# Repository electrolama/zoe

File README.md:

# zoe

A PoE powered Zigbee dev kit with RTC for Raspberry Pi.

Details at [electrolama.com/p/zoe](https://electrolama.com/projects/zoe).

zoe is designed by Electrolama / Omer Kilic and licensed under the [Solderpad Hardware License 2.0](https://solderpad.org/licenses/SHL-2.0/).

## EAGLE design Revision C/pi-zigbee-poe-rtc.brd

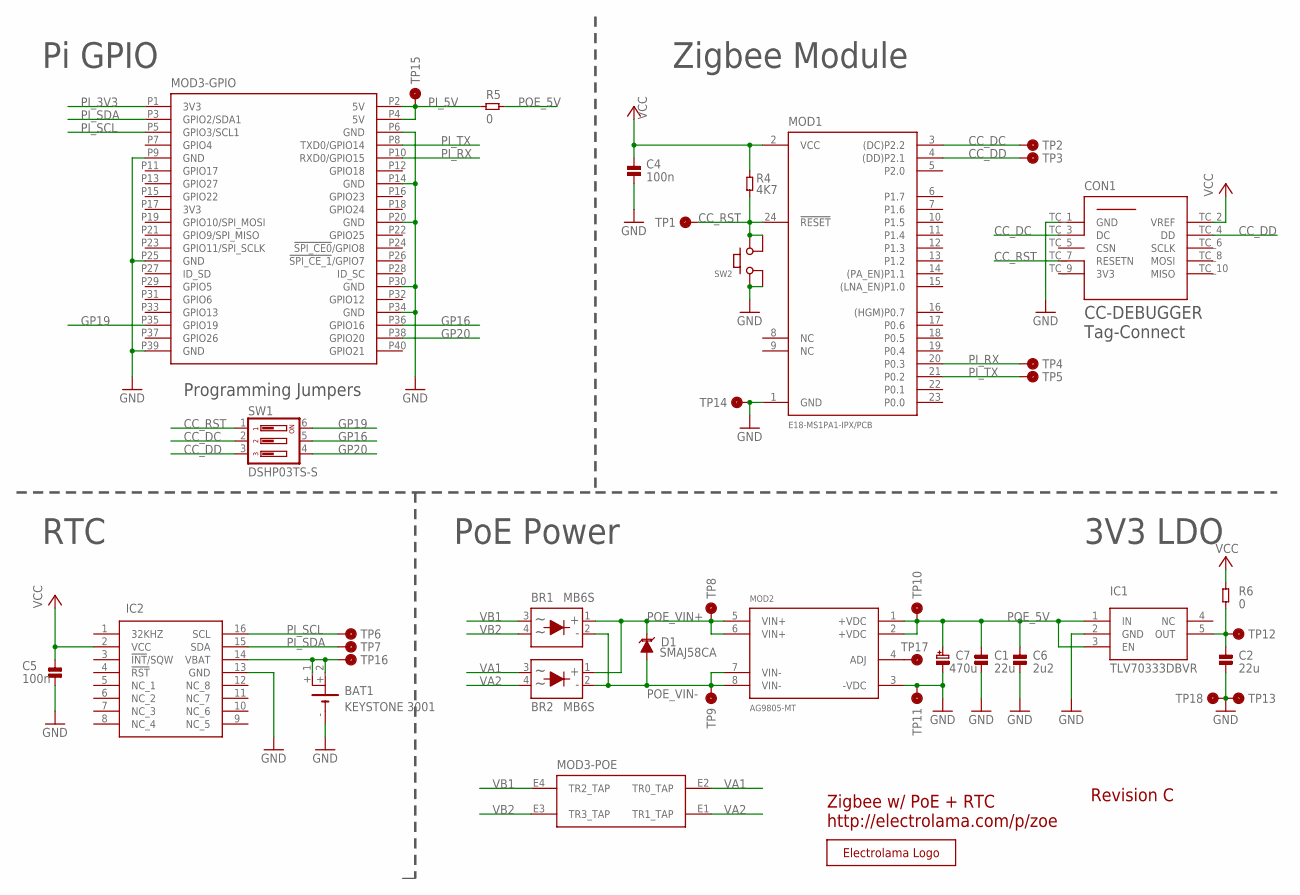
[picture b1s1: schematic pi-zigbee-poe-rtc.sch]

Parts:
BAT1: KEYSTONE 3001; KEYSTONE_3001
BR1, BR2: MB6S; SOP254P665X270-4N
C1, C2: 22u; _PKG_C_0805
C4, C5: 100n; _PKG_C_0603
C6: 2u2; _PKG_C_0603
C7: 470u; _CAP_ELCO_D8_L10.5
CON1: TC2050-IDC-NL_CC-DEBUGGER; TC2050-IDC-NL
D1: SMAJ58CA; DIOM5126X250N-NOPOL
IC1: TLV70333DBVR; SOT95P280X145-5N
IC2: RTC-DS3231SN#; SOIC127P1032X265-16N
MOD1: E18-MS1PA1-IPX/PCB; EBYTE-E18-MS1PA1
MOD2: AG9805-MT; SILVERTEL_AG9800M
MOD3: RPI-HAT-FULL
R4: 4K7; _PKG_C_0603
R5, R6: 0; TP_DUAL_1206
SW1: DSHP03TS-S
SW2: SPNO-XKB-TS-1187A; XKB-TS-1187A
TP1, TP2, TP3, TP4, TP5, TP6, TP7, TP8, TP9, TP10, TP11, TP12, TP13, TP14, TP15, TP16, TP17: TP; TP_DOT
TP18: TP-HOOK; TP_S2751-46R
U$1: LOGO-ELECTROLAMA; ELECTROLAMA

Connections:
CC_DC: CON1.TC_3 (DC), MOD1.3 ((DC)P2.2), SW1.2, TP2.TP
CC_DD: CON1.TC_4 (DD), MOD1.4 ((DD)P2.1), SW1.3, TP3.TP
CC_RST: CON1.TC_7 (RESETN), MOD1.24 (!RESET), R4.1, SW1.1, SW2.C (2_1), SW2.D (2_2), TP1.TP
GND: BAT1.-, C1.1, C2.1, C4.2, C5.2, C6.2, C7.-, CON1.TC_1 (GND), IC1.2 (GND), IC2.13 (GND), MOD1.1 (GND), MOD2.3 (-VDC), MOD3.P6 (GND), MOD3.P9 (GND), MOD3.P14 (GND), MOD3.P20 (GND), MOD3.P25 (GND), MOD3.P30 (GND), MOD3.P34 (GND), MOD3.P39 (GND), SW2.A (1_1), SW2.B (1_2), TP11.TP, TP13.TP, TP14.TP, TP18.1
GP16: MOD3.P36 (GPIO16), SW1.5
GP19: MOD3.P35 (GPIO19), SW1.6
GP20: MOD3.P38 (GPIO20), SW1.4
LDO_OUT: C2.2, IC1.5 (OUT), R6.1, TP12.TP
unnamed: BAT1.+_1 (+1), BAT1.+_2 (+2), IC2.14 (VBAT), TP16.TP
PI_3V3: MOD3.P1 (3V3)
PI_5V: MOD3.P2 (5V), MOD3.P4 (5V), R5.1, TP15.TP
PI_RX: MOD1.20 (P0.3), MOD3.P10 (RXD0/GPIO15), TP4.TP
PI_SCL: IC2.16 (SCL), MOD3.P5 (GPIO3/SCL1), TP6.TP
PI_SDA: IC2.15 (SDA), MOD3.P3 (GPIO2/SDA1), TP7.TP
PI_TX: MOD1.21 (P0.2), MOD3.P8 (TXD0/GPIO14), TP5.TP
POE_5V: C1.2, C6.1, C7.+, IC1.1 (IN), IC1.3 (EN), MOD2.1 (+VDC), MOD2.2 (+VDC), R5.2, TP10.TP
POE_ADJ: MOD2.4 (ADJ), TP17.TP
POE_VIN+: BR1.1 (+), BR2.1 (+), D1.1 (C), MOD2.5 (VIN+), MOD2.6 (VIN+), TP8.TP
POE_VIN-: BR1.2 (-), BR2.2 (-), D1.2 (A), MOD2.7 (VIN-), MOD2.8 (VIN-), TP9.TP
VA1: BR2.3, MOD3.E2 (TR0_TAP)
VA2: BR2.4, MOD3.E1 (TR1_TAP)
VB1: BR1.3, MOD3.E4 (TR2_TAP)
VB2: BR1.4, MOD3.E3 (TR3_TAP)
VCC: C4.1, C5.1, CON1.TC_2 (VREF), IC2.2 (VCC), MOD1.2 (VCC), R4.2, R6.2

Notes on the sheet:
RTC
Pi GPIO
Zigbee Module
PoE Power
3V3 LDO
Zigbee w/ PoE + RTC http://electrolama.com/p/zoe
Revision C
CC-DEBUGGER Tag-Connect
Programming Jumpers

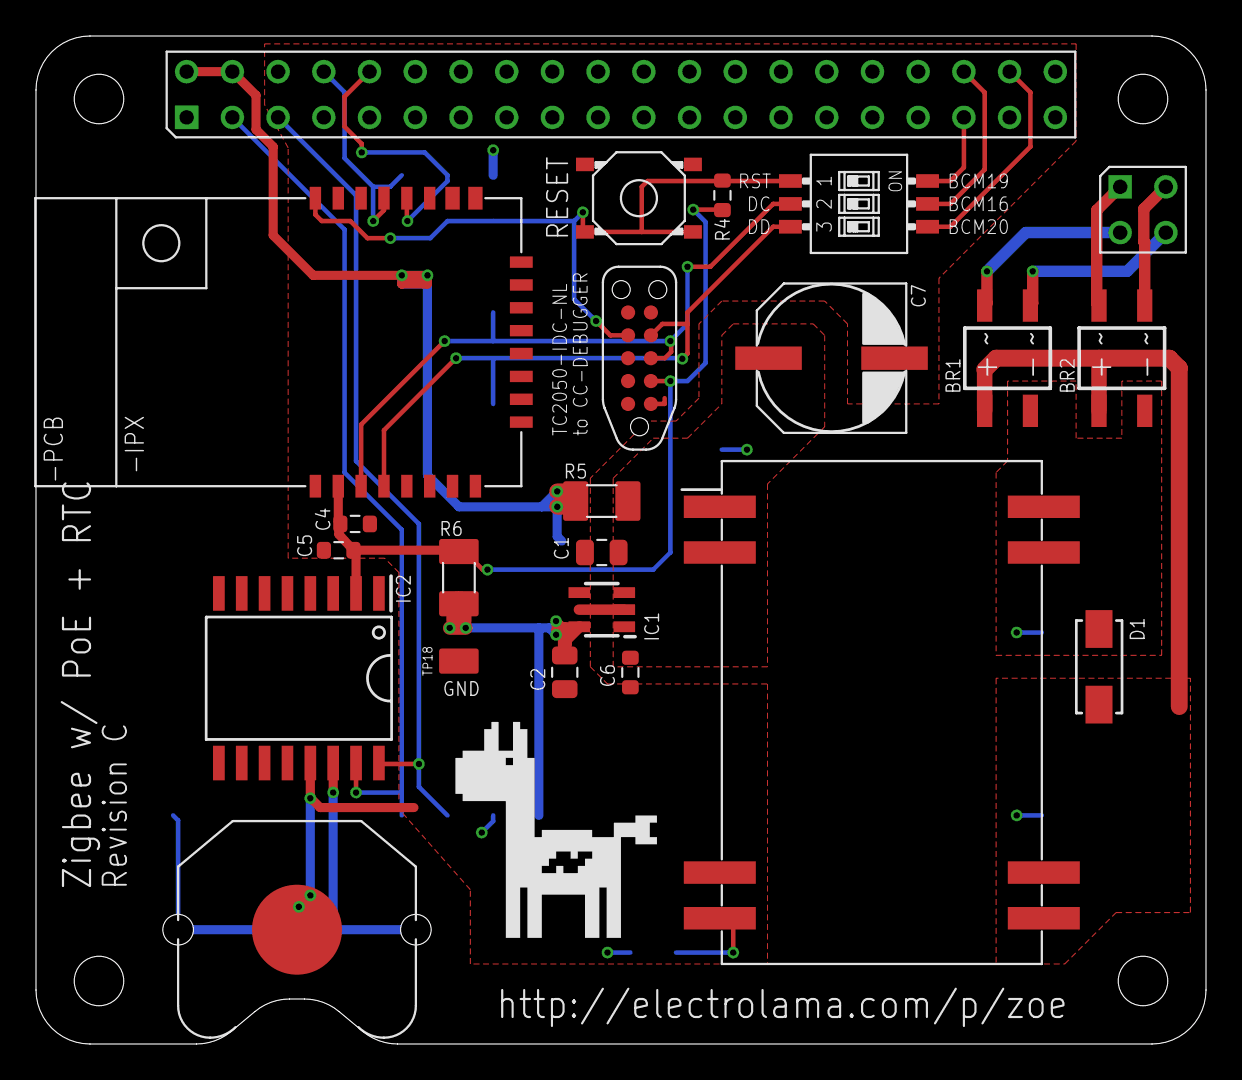
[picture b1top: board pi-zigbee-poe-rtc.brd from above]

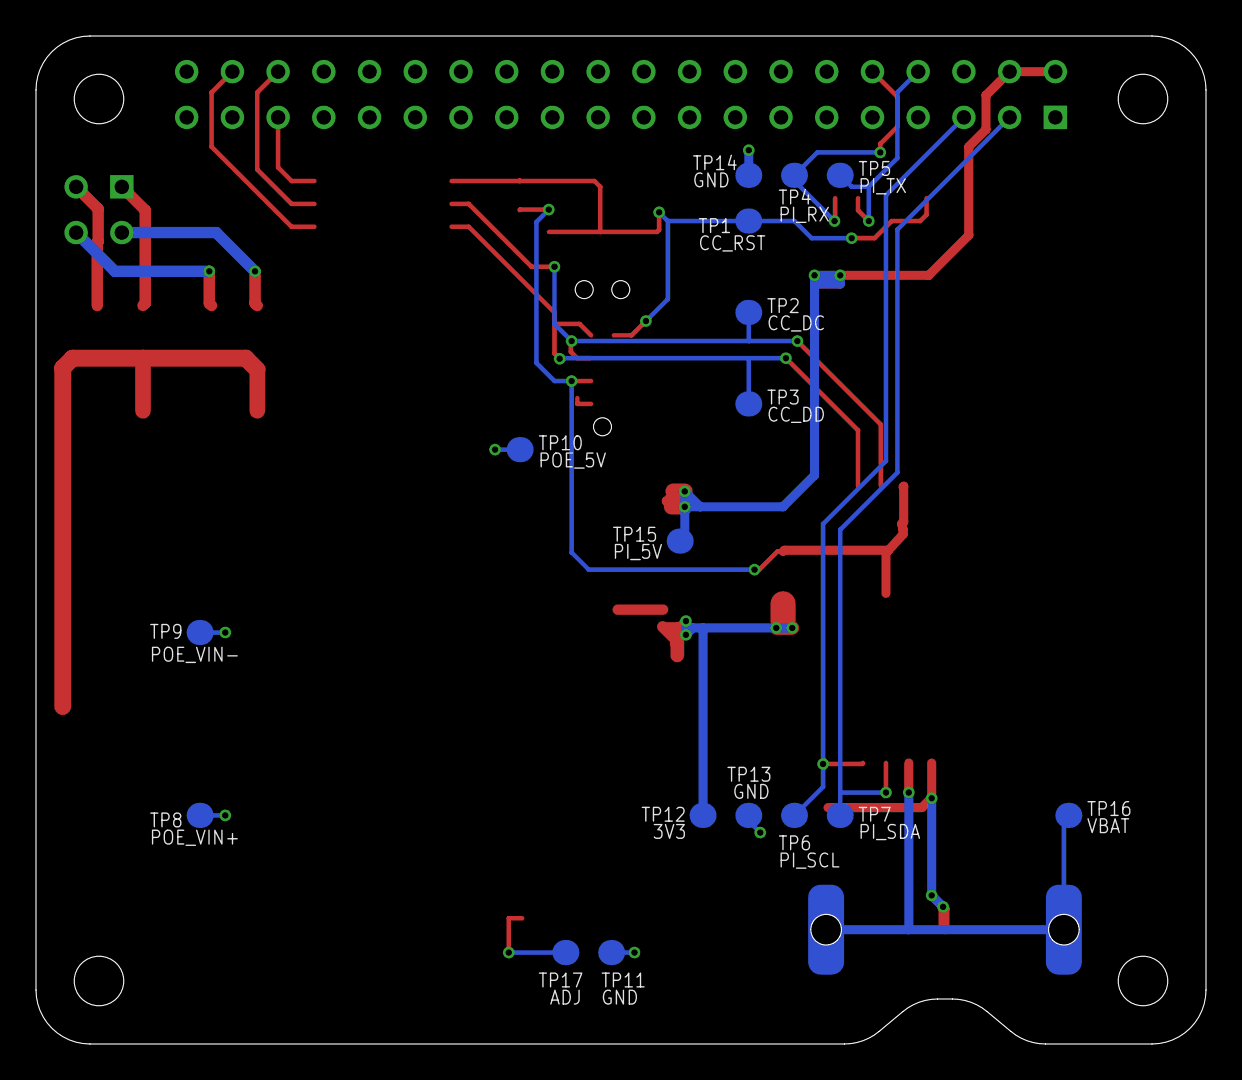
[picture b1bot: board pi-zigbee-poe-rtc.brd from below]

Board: 2 copper layers, 65.0 x 56.0 mm, 40 parts (17 on the bottom side), 23 nets.

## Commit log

2020-01-02 add ignores
2020-01-02 add revision A files
2020-01-02 add revision B files
2020-01-02 add revision C files
2020-01-02 add changelog
2020-01-02 add license, update readme
